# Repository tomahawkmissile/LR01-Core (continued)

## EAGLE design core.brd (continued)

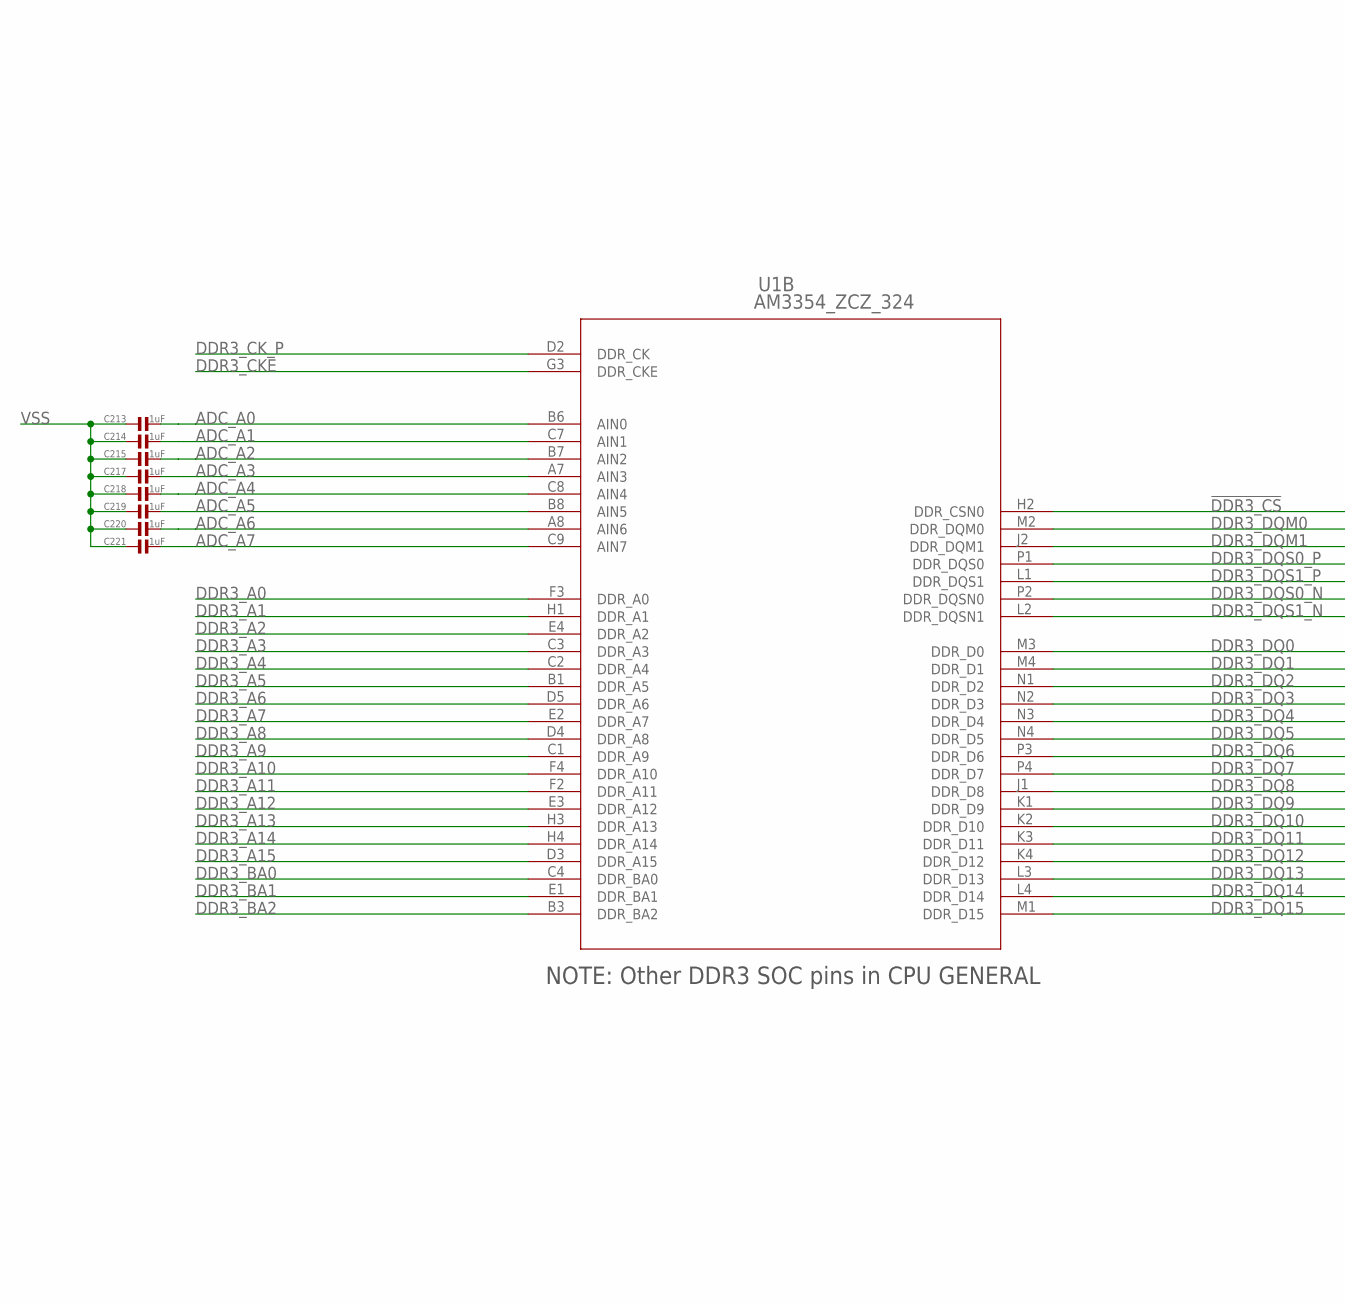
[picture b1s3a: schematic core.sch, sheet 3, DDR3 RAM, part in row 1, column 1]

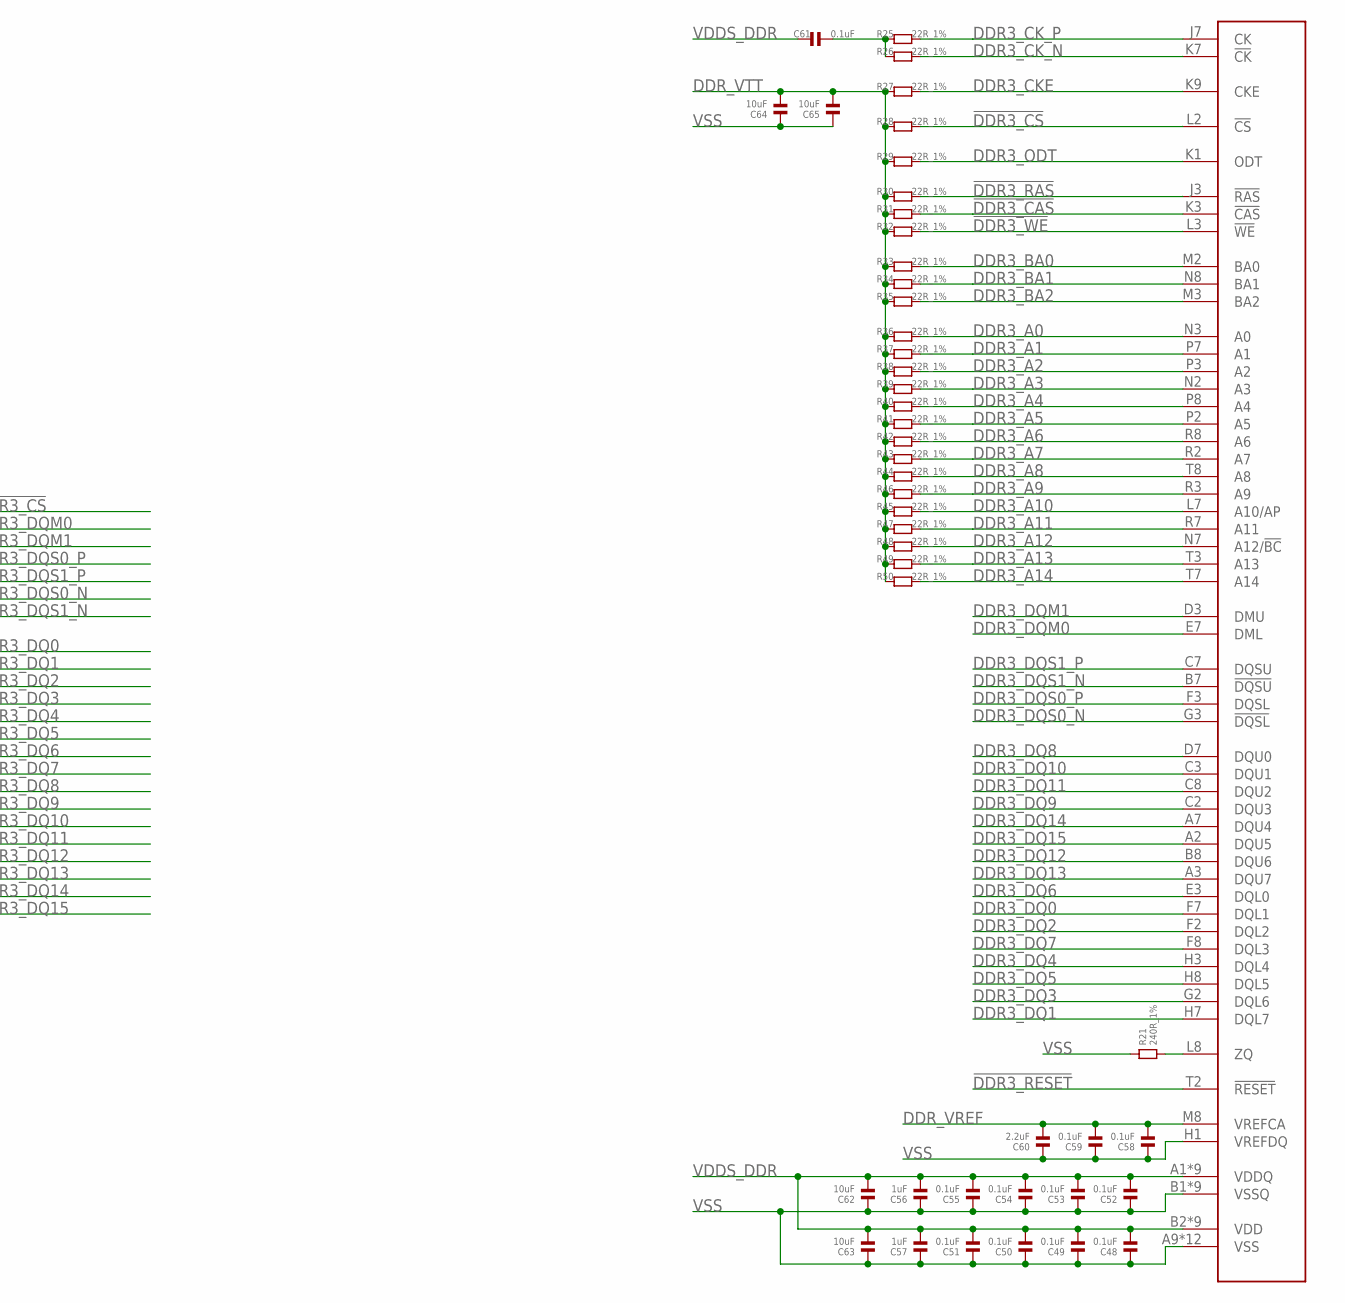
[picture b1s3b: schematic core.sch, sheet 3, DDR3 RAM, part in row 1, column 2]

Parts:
C48, C49, C50, C51, C52, C53, C54, C55, C59: 0.1uF; 0402
C56, C57, C213, C214, C215, C217, C218, C219, C220, C221: 1uF; 0402
C58, C61: 0.1uF; 0201
C60: 2.2uF; 0603
C62, C63: 10uF; 0603
C64, C65: 10uF; 0402
R21: 240R_1%; 0402
R25, R26, R27, R28, R29, R30, R31, R32, R33, R34, R35, R36, R37, R38, R39, R40, R41, R42, R43, R44, R45, R46, R47, R48, R49, R50: 22R_1%; 0201
U1: AM3354_ZCZ_324; ZCZ324
U9: AS4C256M16D3B-12BIN; BGA144C80P9X16_1350X900X120

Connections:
!DDR3_CAS: R31.2, U9.K3 (!CAS); also elsewhere on the board
!DDR3_CS: R28.2, U1.H2 (DDR_CSN0), U9.L2 (!CS)
!DDR3_RAS: R30.2, U9.J3 (!RAS); also elsewhere on the board
!DDR3_RESET: U9.T2 (!RESET); also elsewhere on the board
!DDR3_WE: R32.2, U9.L3 (!WE); also elsewhere on the board
ADC_A0: C213.2, U1.B6 (AIN0); also elsewhere on the board
ADC_A1: C214.2, U1.C7 (AIN1); also elsewhere on the board
ADC_A2: C215.2, U1.B7 (AIN2); also elsewhere on the board
ADC_A3: C217.2, U1.A7 (AIN3); also elsewhere on the board
ADC_A4: C218.2, U1.C8 (AIN4); also elsewhere on the board
ADC_A5: C219.2, U1.B8 (AIN5); also elsewhere on the board
ADC_A6: C220.2, U1.A8 (AIN6); also elsewhere on the board
ADC_A7: C221.2, U1.C9 (AIN7); also elsewhere on the board
DDR3_A0: R36.2, U1.F3 (DDR_A0), U9.N3 (A0)
DDR3_A1: R37.2, U1.H1 (DDR_A1), U9.P7 (A1)
DDR3_A2: R38.2, U1.E4 (DDR_A2), U9.P3 (A2)
DDR3_A3: R39.2, U1.C3 (DDR_A3), U9.N2 (A3)
DDR3_A4: R40.2, U1.C2 (DDR_A4), U9.P8 (A4)
DDR3_A5: R41.2, U1.B1 (DDR_A5), U9.P2 (A5)
DDR3_A6: R42.2, U1.D5 (DDR_A6), U9.R8 (A6)
DDR3_A7: R43.2, U1.E2 (DDR_A7), U9.R2 (A7)
DDR3_A8: R44.2, U1.D4 (DDR_A8), U9.T8 (A8)
DDR3_A9: R46.2, U1.C1 (DDR_A9), U9.R3 (A9)
DDR3_A10: R45.2, U1.F4 (DDR_A10), U9.L7 (A10/AP)
DDR3_A11: R47.2, U1.F2 (DDR_A11), U9.R7 (A11)
DDR3_A12: R48.2, U1.E3 (DDR_A12), U9.N7 (A12/!BC)
DDR3_A13: R49.2, U1.H3 (DDR_A13), U9.T3 (A13)
DDR3_A14: R50.2, U1.H4 (DDR_A14), U9.T7 (A14)
DDR3_A15: U1.D3 (DDR_A15)
DDR3_BA0: R33.2, U1.C4 (DDR_BA0), U9.M2 (BA0)
DDR3_BA1: R34.2, U1.E1 (DDR_BA1), U9.N8 (BA1)
DDR3_BA2: R35.2, U1.B3 (DDR_BA2), U9.M3 (BA2)
DDR3_CKE: R27.2, U1.G3 (DDR_CKE), U9.K9 (CKE)
DDR3_CK_N: R26.2, U9.K7 (!CK); also elsewhere on the board
DDR3_CK_P: R25.2, U1.D2 (DDR_CK), U9.J7 (CK)
DDR3_DQ0: U1.M3 (DDR_D0), U9.F7 (DQL1)
DDR3_DQ1: U1.M4 (DDR_D1), U9.H7 (DQL7)
DDR3_DQ2: U1.N1 (DDR_D2), U9.F2 (DQL2)
DDR3_DQ3: U1.N2 (DDR_D3), U9.G2 (DQL6)
DDR3_DQ4: U1.N3 (DDR_D4), U9.H3 (DQL4)
DDR3_DQ5: U1.N4 (DDR_D5), U9.H8 (DQL5)
DDR3_DQ6: U1.P3 (DDR_D6), U9.E3 (DQL0)
DDR3_DQ7: U1.P4 (DDR_D7), U9.F8 (DQL3)
DDR3_DQ8: U1.J1 (DDR_D8), U9.D7 (DQU0)
DDR3_DQ9: U1.K1 (DDR_D9), U9.C2 (DQU3)
DDR3_DQ10: U1.K2 (DDR_D10), U9.C3 (DQU1)
DDR3_DQ11: U1.K3 (DDR_D11), U9.C8 (DQU2)
DDR3_DQ12: U1.K4 (DDR_D12), U9.B8 (DQU6)
DDR3_DQ13: U1.L3 (DDR_D13), U9.A3 (DQU7)
DDR3_DQ14: U1.L4 (DDR_D14), U9.A7 (DQU4)
DDR3_DQ15: U1.M1 (DDR_D15), U9.A2 (DQU5)
DDR3_DQM0: U1.M2 (DDR_DQM0), U9.E7 (DML)
DDR3_DQM1: U1.J2 (DDR_DQM1), U9.D3 (DMU)
DDR3_DQS0_N: U1.P2 (DDR_DQSN0), U9.G3 (!DQSL)
DDR3_DQS0_P: U1.P1 (DDR_DQS0), U9.F3 (DQSL)
DDR3_DQS1_N: U1.L2 (DDR_DQSN1), U9.B7 (!DQSU)
DDR3_DQS1_P: U1.L1 (DDR_DQS1), U9.C7 (DQSU)
DDR3_ODT: R29.2, U9.K1 (ODT); also elsewhere on the board
DDR_VREF: C58.2, C59.2, C60.2, U9.M8 (VREFCA); also elsewhere on the board
DDR_VTT: C64.2, C65.2, R27.1, R28.1, R29.1, R30.1, R31.1, R32.1, R33.1, R34.1, R35.1, R36.1, R37.1, R38.1, R39.1, R40.1, R41.1, R42.1, R43.1, R44.1, R45.1, R46.1, R47.1, R48.1, R49.1, R50.1; also elsewhere on the board
unnamed: R21.2, U9.L8 (ZQ)
unnamed: C61.2, R25.1, R26.1
VDDS_DDR: C48.2, C49.2, C50.2, C51.2, C52.2, C53.2, C54.2, C55.2, C56.2, C57.2, C61.1, C62.2, C63.2, U9.A1 (VDDQ), U9.A8 (VDDQ), U9.B2 (VDD), U9.C1 (VDDQ), U9.C9 (VDDQ), U9.D2 (VDDQ), U9.D9 (VDD), U9.E9 (VDDQ), U9.F1 (VDDQ), U9.G7 (VDD), U9.H2 (VDDQ), U9.H9 (VDDQ), U9.K2 (VDD), U9.K8 (VDD), U9.N1 (VDD), U9.N9 (VDD), U9.R1 (VDD), U9.R9 (VDD); also elsewhere on the board
VPP: U1.M5 (VPP)
VSS: C48.1, C49.1, C50.1, C51.1, C52.1, C53.1, C54.1, C55.1, C56.1, C57.1, C58.1, C59.1, C60.1, C62.1, C63.1, C64.1, C65.1, C213.1, C214.1, C215.1, C217.1, C218.1, C219.1, C220.1, C221.1, R21.1, U9.A9 (VSS), U9.B1 (VSSQ), U9.B3 (VSS), U9.B9 (VSSQ), U9.D1 (VSSQ), U9.D8 (VSSQ), U9.E1 (VSS), U9.E2 (VSSQ), U9.E8 (VSSQ), U9.F9 (VSSQ), U9.G1 (VSSQ), U9.G8 (VSS), U9.G9 (VSSQ), U9.H1 (VREFDQ), U9.J2 (VSS), U9.J8 (VSS), U9.M1 (VSS), U9.M9 (VSS), U9.P1 (VSS), U9.P9 (VSS), U9.T1 (VSS), U9.T9 (VSS); also elsewhere on the board

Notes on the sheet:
NOTE: Other DDR3 SOC pins in CPU GENERAL

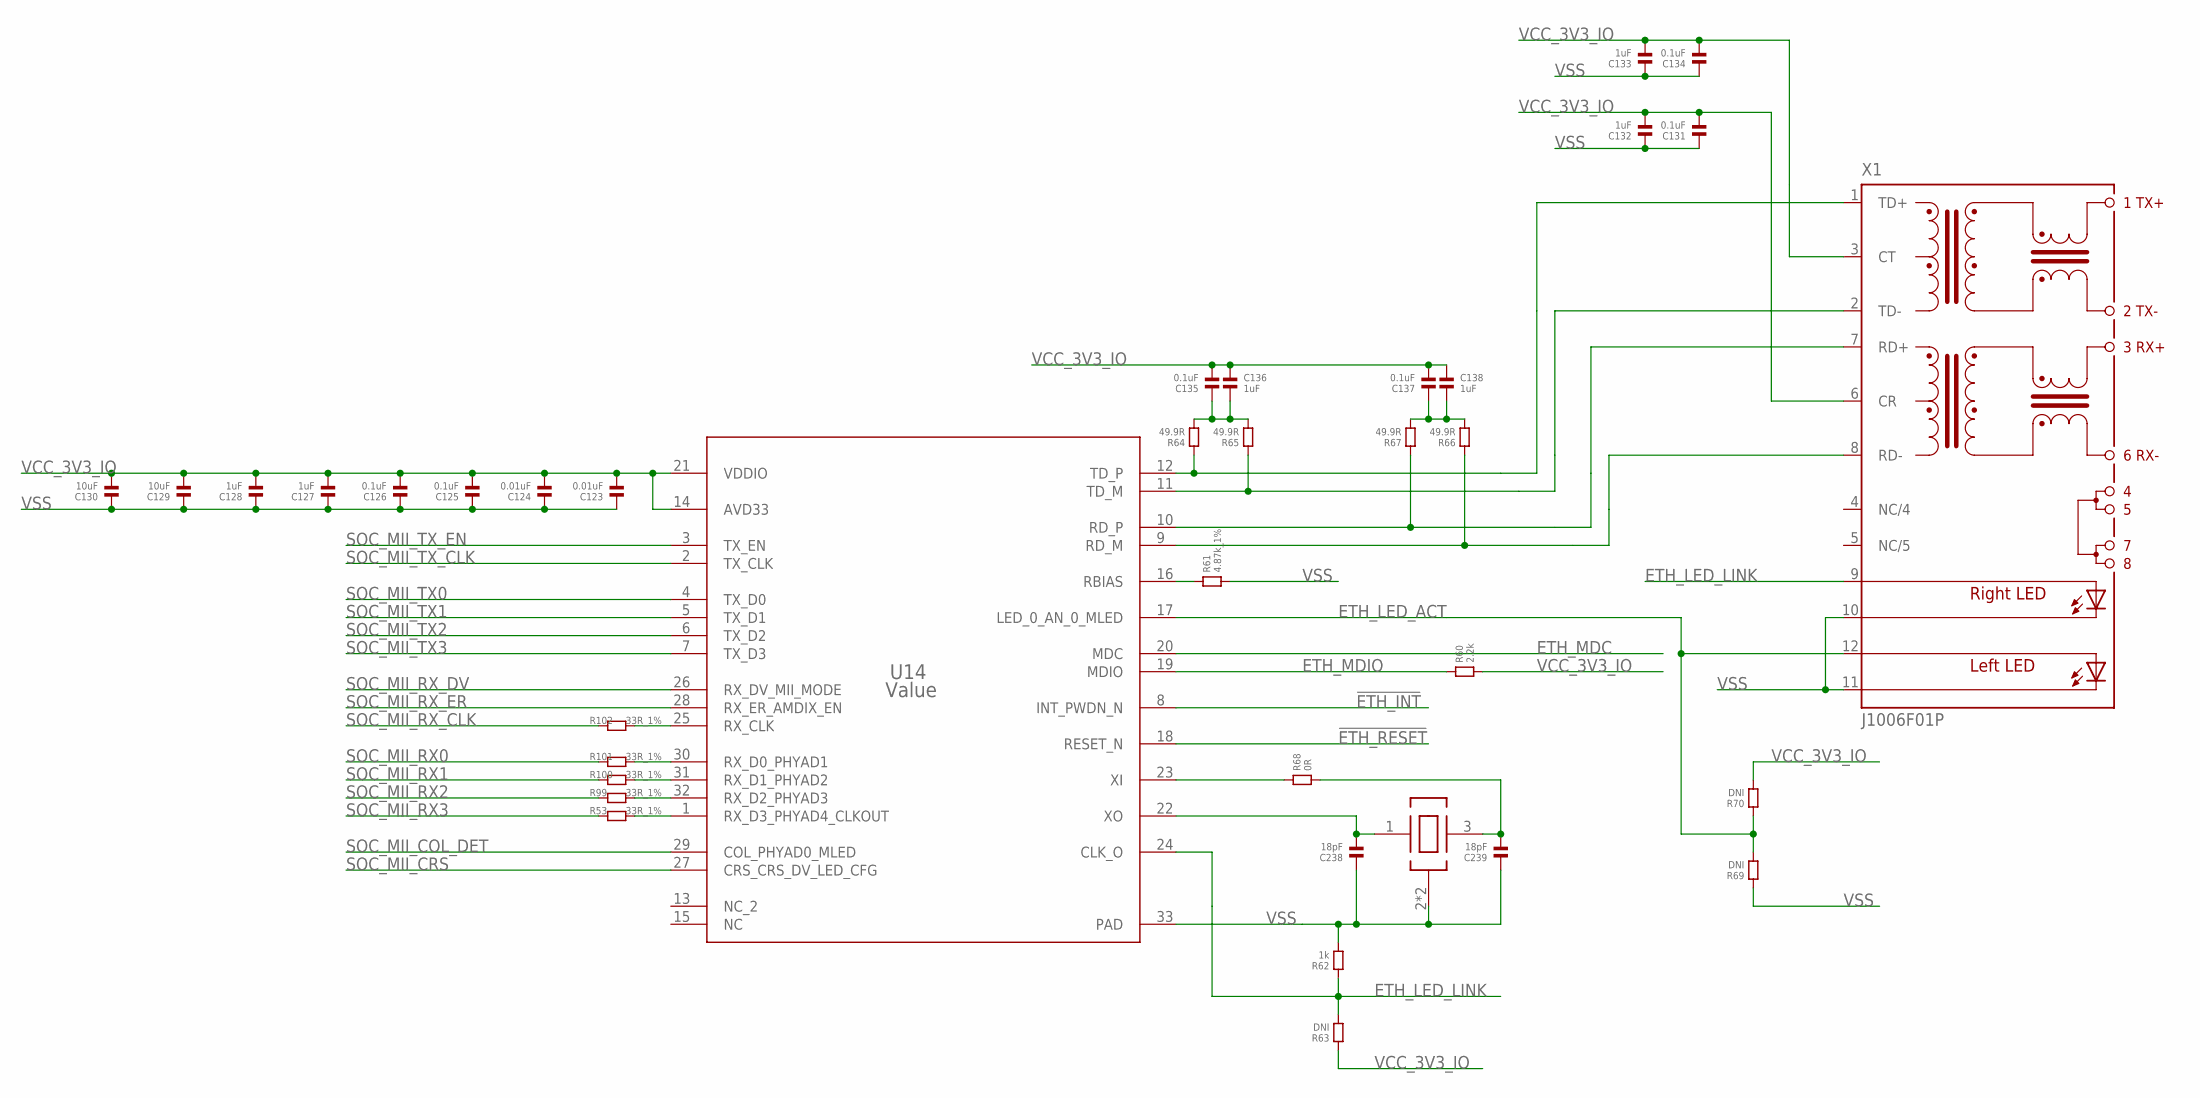
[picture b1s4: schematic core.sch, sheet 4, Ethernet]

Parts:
C123, C124: 0.01uF; 0402
C125, C126, C131, C134, C135, C137: 0.1uF; 0402
C127, C128, C132, C133, C136, C138: 1uF; 0402
C129, C130: 10uF; 0402
C238, C239: 18pF; 0402
R53, R99, R100, R101, R102: 33R_1%; 0402
R60: 2.2k; 0402
R61: 4.87k_1%; 0402
R62: 1k; 0402
R63, R69, R70: DNI; 0402
R64, R65, R66, R67: 49.9R; 0402
R68: 0R; 0402
U14: Value; RHB0032B
U$7: ECS-250-18-36B-CKY-TR; OSCCC250X200X65
X1: J1006F01P; J1

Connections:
!ETH_INT: U14.8 (INT_PWDN_N); also elsewhere on the board
!ETH_RESET: U14.18 (RESET_N); also elsewhere on the board
ETH_LED_ACT: R69.2, R70.1, U14.17 (LED_0_AN_0_MLED), X1.12 (A-L)
ETH_LED_LINK: R62.1, R63.2, U14.24 (CLK_O), X1.9 (A-R)
ETH_MDC: U14.20 (MDC); also elsewhere on the board
ETH_MDIO: R60.1, U14.19 (MDIO); also elsewhere on the board
unnamed: R61.1, U14.16 (RBIAS)
unnamed: C238.2, U14.22 (XO), U$7.1 (XI)
unnamed: C239.2, R68.2, U$7.3 (XO)
unnamed: R66.1, U14.9 (RD_M), X1.8 (RD-)
unnamed: R67.1, U14.10 (RD_P), X1.7 (RD+)
unnamed: C135.1, C136.2, R64.2, R65.2
unnamed: R68.1, U14.23 (XI)
unnamed: C137.1, C138.2, R66.2, R67.2
unnamed: R65.1, U14.11 (TD_M), X1.2 (TD-)
unnamed: R64.1, U14.12 (TD_P), X1.1 (TD+)
unnamed: R53.2, U14.1 (RX_D3_PHYAD4_CLKOUT)
unnamed: R99.2, U14.32 (RX_D2_PHYAD3)
unnamed: R100.2, U14.31 (RX_D1_PHYAD2)
unnamed: R101.2, U14.30 (RX_D0_PHYAD1)
unnamed: R102.2, U14.25 (RX_CLK)
SOC_MII_COL_DET: U14.29 (COL_PHYAD0_MLED); also elsewhere on the board
SOC_MII_CRS: U14.27 (CRS_CRS_DV_LED_CFG); also elsewhere on the board
SOC_MII_RX0: R101.1; also elsewhere on the board
SOC_MII_RX1: R100.1; also elsewhere on the board
SOC_MII_RX2: R99.1; also elsewhere on the board
SOC_MII_RX3: R53.1; also elsewhere on the board
SOC_MII_RX_CLK: R102.1; also elsewhere on the board
SOC_MII_RX_DV: U14.26 (RX_DV_MII_MODE); also elsewhere on the board
SOC_MII_RX_ER: U14.28 (RX_ER_AMDIX_EN); also elsewhere on the board
SOC_MII_TX0: U14.4 (TX_D0); also elsewhere on the board
SOC_MII_TX1: U14.5 (TX_D1); also elsewhere on the board
SOC_MII_TX2: U14.6 (TX_D2); also elsewhere on the board
SOC_MII_TX3: U14.7 (TX_D3); also elsewhere on the board
SOC_MII_TX_CLK: U14.2 (TX_CLK); also elsewhere on the board
SOC_MII_TX_EN: U14.3 (TX_EN); also elsewhere on the board
VCC_3V3_IO: C123.2, C124.2, C125.2, C126.2, C127.2, C128.2, C129.2, C130.2, C131.2, C132.2, C133.2, C134.2, C135.2, C136.1, C137.2, C138.1, R60.2, R63.1, R70.2, U14.14 (AVD33), U14.21 (VDDIO), X1.3 (CT), X1.6 (CR); also elsewhere on the board
VSS: C123.1, C124.1, C125.1, C126.1, C127.1, C128.1, C129.1, C130.1, C131.1, C132.1, C133.1, C134.1, C238.1, C239.1, R61.2, R62.2, R69.1, U14.33 (PAD), U$7.2 (VSS), U$7.4 (VSS), X1.10 (C-R), X1.11 (C-L); also elsewhere on the board

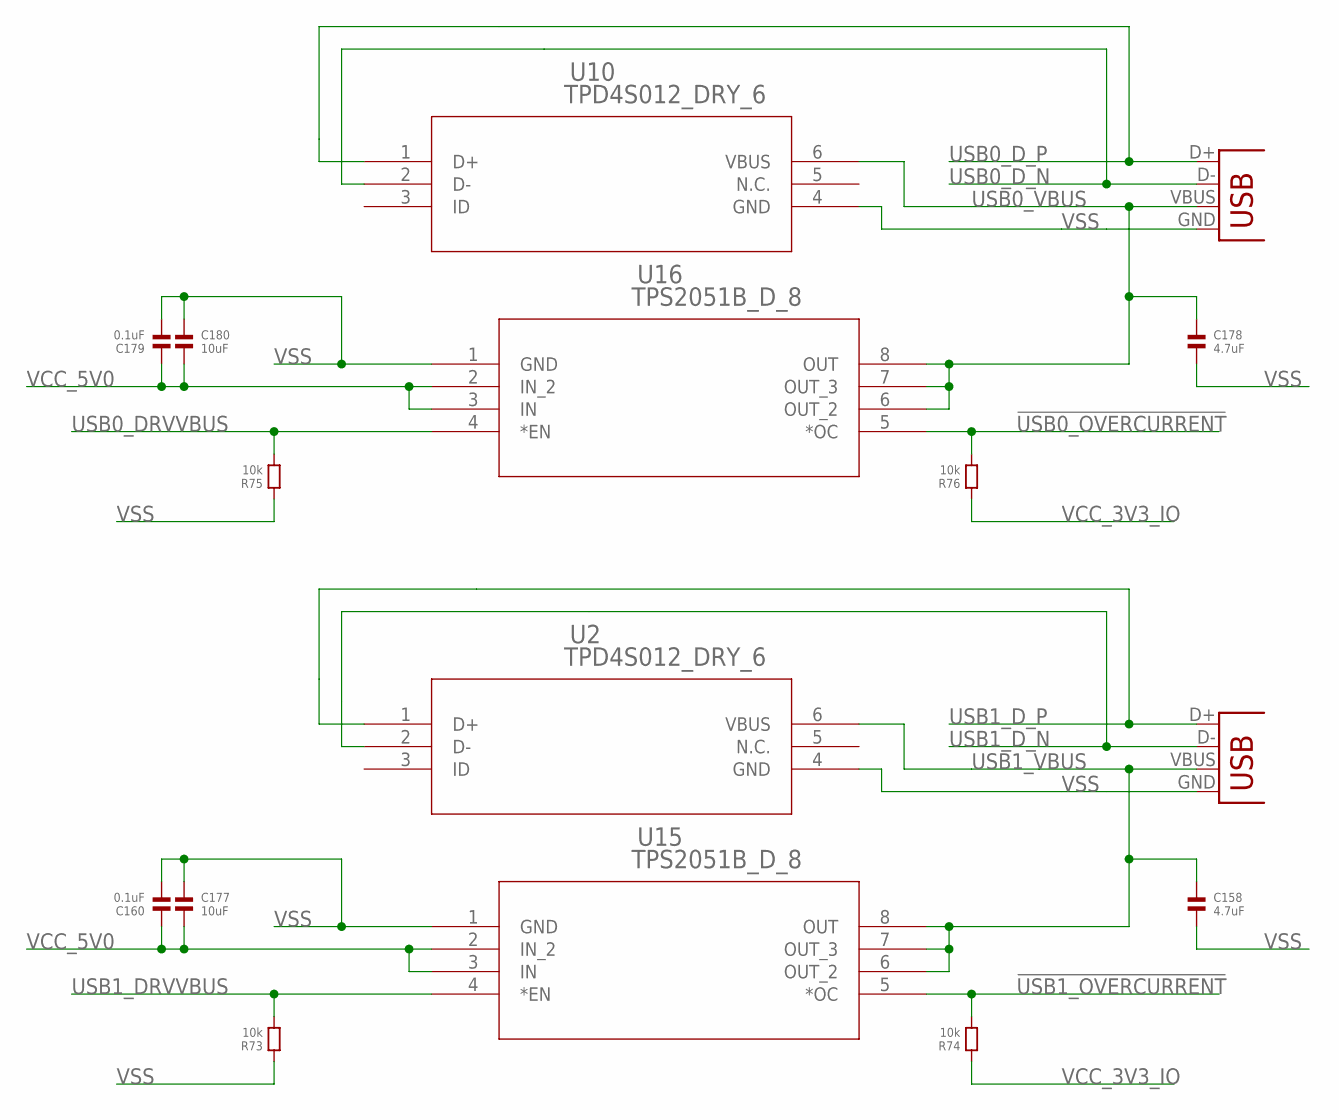
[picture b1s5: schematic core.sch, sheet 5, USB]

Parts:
C158, C178: 4.7uF; 0603
C160, C179: 0.1uF; 0603
C177, C180: 10uF; 0603
R73, R74, R75, R76: 10k; 0402
U2, U10: TPD4S012_DRY_6; DRY6
U15, U16: TPS2051B_D_8; D8
X2, X3: USB-A-H

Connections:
!USB0_OVERCURRENT: R76.2, U16.5 (*OC); also elsewhere on the board
!USB1_OVERCURRENT: R74.2, U15.5 (*OC); also elsewhere on the board
USB0_DRVVBUS: R75.2, U16.4 (*EN); also elsewhere on the board
USB0_D_N: U10.2 (D-), X3.D-; also elsewhere on the board
USB0_D_P: U10.1 (D+), X3.D+; also elsewhere on the board
USB0_VBUS: C178.1, U10.6 (VBUS), U16.6 (OUT_2), U16.7 (OUT_3), U16.8 (OUT), X3.VBUS; also elsewhere on the board
USB1_DRVVBUS: R73.2, U15.4 (*EN); also elsewhere on the board
USB1_D_N: U2.2 (D-), X2.D-; also elsewhere on the board
USB1_D_P: U2.1 (D+), X2.D+; also elsewhere on the board
USB1_VBUS: C158.1, U2.6 (VBUS), U15.6 (OUT_2), U15.7 (OUT_3), U15.8 (OUT), X2.VBUS; also elsewhere on the board
VCC_3V3_IO: R74.1, R76.1; also elsewhere on the board
VCC_5V0: C160.1, C177.2, C179.1, C180.2, U15.2 (IN_2), U15.3 (IN), U16.2 (IN_2), U16.3 (IN); also elsewhere on the board
VSS: C158.2, C160.2, C177.1, C178.2, C179.2, C180.1, R73.1, R75.1, U2.4 (GND), U10.4 (GND), U15.1 (GND), U16.1 (GND), X2.GND, X3.GND; also elsewhere on the board

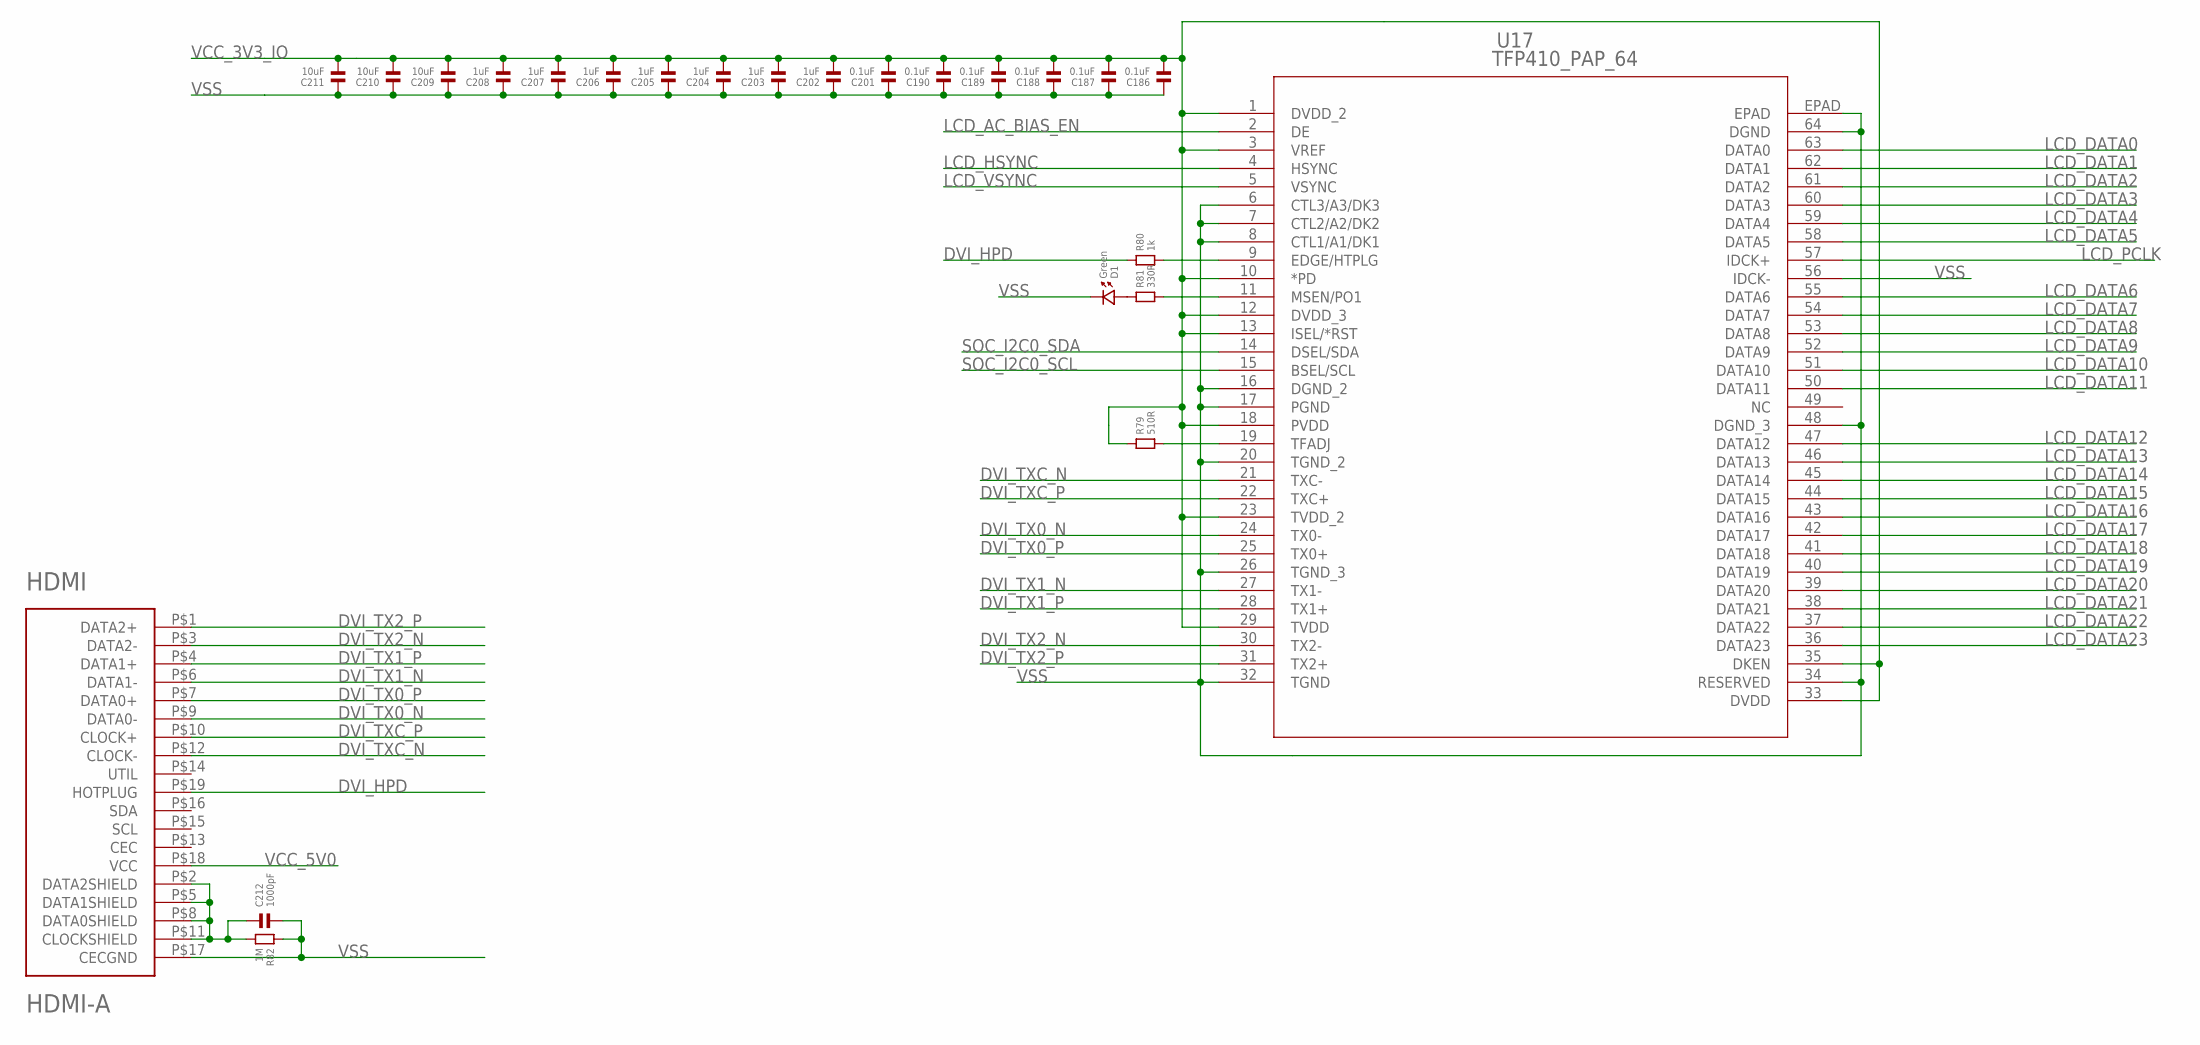
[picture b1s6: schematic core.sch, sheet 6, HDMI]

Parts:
C186, C187, C188, C189, C190, C201: 0.1uF; 0402
C202, C203, C204, C205, C206, C207, C208: 1uF; 0402
C209, C210, C211: 10uF; 0603
C212: 1000pF; 0402
D1: Green; 0603.LED
HDMI: HDMI-A; HDMI_A
R79: 510R; 0402
R80: 1k; 0402
R81: 330R; 0402
R82: 1M; 0402
U17: TFP410_PAP_64; PAP64_5X5

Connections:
DVI_HPD: HDMI.P$19 (HOTPLUG), R80.1
DVI_TX0_N: HDMI.P$9 (DATA0-), U17.24 (TX0-)
DVI_TX0_P: HDMI.P$7 (DATA0+), U17.25 (TX0+)
DVI_TX1_N: HDMI.P$6 (DATA1-), U17.27 (TX1-)
DVI_TX1_P: HDMI.P$4 (DATA1+), U17.28 (TX1+)
DVI_TX2_N: HDMI.P$3 (DATA2-), U17.30 (TX2-)
DVI_TX2_P: HDMI.P$1 (DATA2+), U17.31 (TX2+)
DVI_TXC_N: HDMI.P$12 (CLOCK-), U17.21 (TXC-)
DVI_TXC_P: HDMI.P$10 (CLOCK+), U17.22 (TXC+)
LCD_AC_BIAS_EN: U17.2 (DE); also elsewhere on the board
LCD_DATA0: U17.63 (DATA0); also elsewhere on the board
LCD_DATA1: U17.62 (DATA1); also elsewhere on the board
LCD_DATA2: U17.61 (DATA2); also elsewhere on the board
LCD_DATA3: U17.60 (DATA3); also elsewhere on the board
LCD_DATA4: U17.59 (DATA4); also elsewhere on the board
LCD_DATA5: U17.58 (DATA5); also elsewhere on the board
LCD_DATA6: U17.55 (DATA6); also elsewhere on the board
LCD_DATA7: U17.54 (DATA7); also elsewhere on the board
LCD_DATA8: U17.53 (DATA8); also elsewhere on the board
LCD_DATA9: U17.52 (DATA9); also elsewhere on the board
LCD_DATA10: U17.51 (DATA10); also elsewhere on the board
LCD_DATA11: U17.50 (DATA11); also elsewhere on the board
LCD_DATA12: U17.47 (DATA12); also elsewhere on the board
LCD_DATA13: U17.46 (DATA13); also elsewhere on the board
LCD_DATA14: U17.45 (DATA14); also elsewhere on the board
LCD_DATA15: U17.44 (DATA15); also elsewhere on the board
LCD_DATA16: U17.43 (DATA16); also elsewhere on the board
LCD_DATA17: U17.42 (DATA17); also elsewhere on the board
LCD_DATA18: U17.41 (DATA18); also elsewhere on the board
LCD_DATA19: U17.40 (DATA19); also elsewhere on the board
LCD_DATA20: U17.39 (DATA20); also elsewhere on the board
LCD_DATA21: U17.38 (DATA21); also elsewhere on the board
LCD_DATA22: U17.37 (DATA22); also elsewhere on the board
LCD_DATA23: U17.36 (DATA23); also elsewhere on the board
LCD_HSYNC: U17.4 (HSYNC); also elsewhere on the board
LCD_PCLK: U17.57 (IDCK+); also elsewhere on the board
LCD_VSYNC: U17.5 (VSYNC); also elsewhere on the board
unnamed: R79.2, U17.19 (TFADJ)
unnamed: R80.2, U17.9 (EDGE/HTPLG)
unnamed: R81.2, U17.11 (MSEN/PO1)
unnamed: D1.P$1 (1), R81.1
unnamed: C212.1, HDMI.P$2 (DATA2SHIELD), HDMI.P$5 (DATA1SHIELD), HDMI.P$8 (DATA0SHIELD), HDMI.P$11 (CLOCKSHIELD), R82.2
SOC_I2C0_SCL: U17.15 (BSEL/SCL); also elsewhere on the board
SOC_I2C0_SDA: U17.14 (DSEL/SDA); also elsewhere on the board
VCC_3V3_IO: C186.2, C187.2, C188.2, C189.2, C190.2, C201.2, C202.2, C203.2, C204.2, C205.2, C206.2, C207.2, C208.2, C209.2, C210.2, C211.2, R79.1, U17.1 (DVDD_2), U17.3 (VREF), U17.10 (*PD), U17.12 (DVDD_3), U17.13 (ISEL/*RST), U17.18 (PVDD), U17.23 (TVDD_2), U17.29 (TVDD), U17.33 (DVDD), U17.35 (DKEN); also elsewhere on the board
VCC_5V0: HDMI.P$18 (VCC); also elsewhere on the board
VSS: C186.1, C187.1, C188.1, C189.1, C190.1, C201.1, C202.1, C203.1, C204.1, C205.1, C206.1, C207.1, C208.1, C209.1, C210.1, C211.1, C212.2, D1.P$2 (2), HDMI.P$17 (CECGND), R82.1, U17.6 (CTL3/A3/DK3), U17.7 (CTL2/A2/DK2), U17.8 (CTL1/A1/DK1), U17.16 (DGND_2), U17.17 (PGND), U17.20 (TGND_2), U17.26 (TGND_3), U17.32 (TGND), U17.34 (RESERVED), U17.48 (DGND_3), U17.56 (IDCK-), U17.64 (DGND), U17.EPAD; also elsewhere on the board

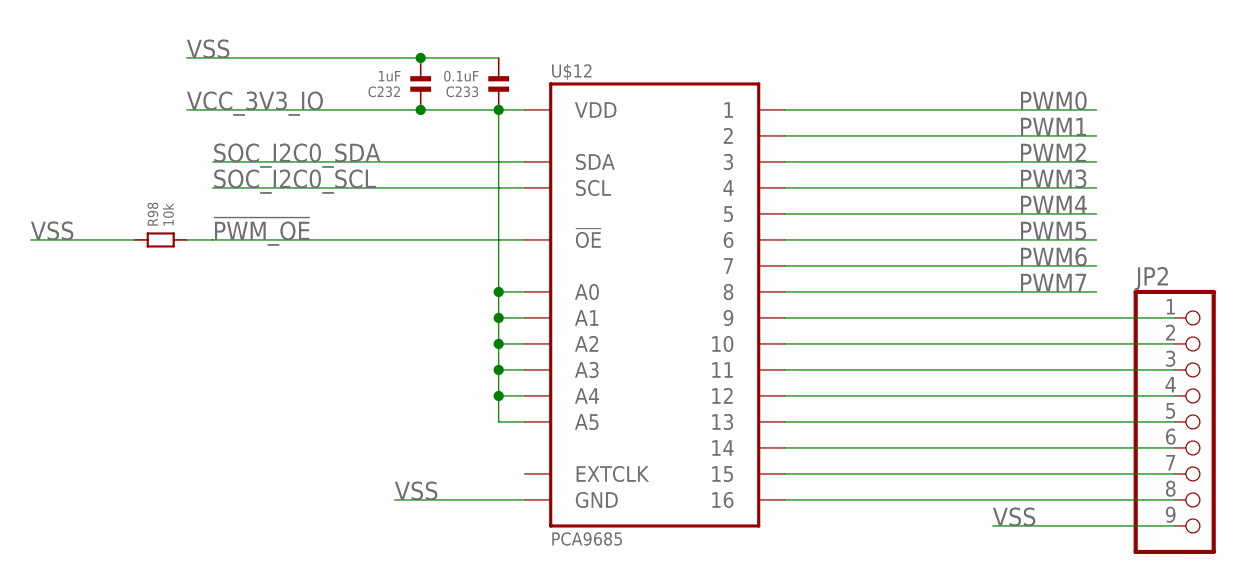
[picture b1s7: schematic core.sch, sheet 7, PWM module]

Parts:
C232: 1uF; 0402
C233: 0.1uF; 0402
JP2: PINHD-1X9; 1X09
R98: 10k; 0402
U$12: PCA9685; HVQFN28

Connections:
!PWM_OE: R98.2, U$12.23 (!OE)
unnamed: JP2.1, U$12.15 (9)
unnamed: JP2.2, U$12.16 (10)
unnamed: JP2.3, U$12.17 (11)
unnamed: JP2.5, U$12.19 (13)
unnamed: JP2.4, U$12.18 (12)
unnamed: JP2.6, U$12.20 (14)
unnamed: JP2.7, U$12.21 (15)
unnamed: JP2.8, U$12.22 (16)
PWM0: U$12.6 (1); also elsewhere on the board
PWM1: U$12.7 (2); also elsewhere on the board
PWM2: U$12.8 (3); also elsewhere on the board
PWM3: U$12.9 (4); also elsewhere on the board
PWM4: U$12.10 (5); also elsewhere on the board
PWM5: U$12.11 (6); also elsewhere on the board
PWM6: U$12.12 (7); also elsewhere on the board
PWM7: U$12.13 (8); also elsewhere on the board
SOC_I2C0_SCL: U$12.26 (SCL); also elsewhere on the board
SOC_I2C0_SDA: U$12.27 (SDA); also elsewhere on the board
VCC_3V3_IO: C232.1, C233.1, U$12.1 (A0), U$12.2 (A1), U$12.3 (A2), U$12.4 (A3), U$12.5 (A4), U$12.24 (A5), U$12.28 (VDD); also elsewhere on the board
VSS: C232.2, C233.2, JP2.9, R98.1, U$12.14 (GND), U$12.PAD (GND); also elsewhere on the board

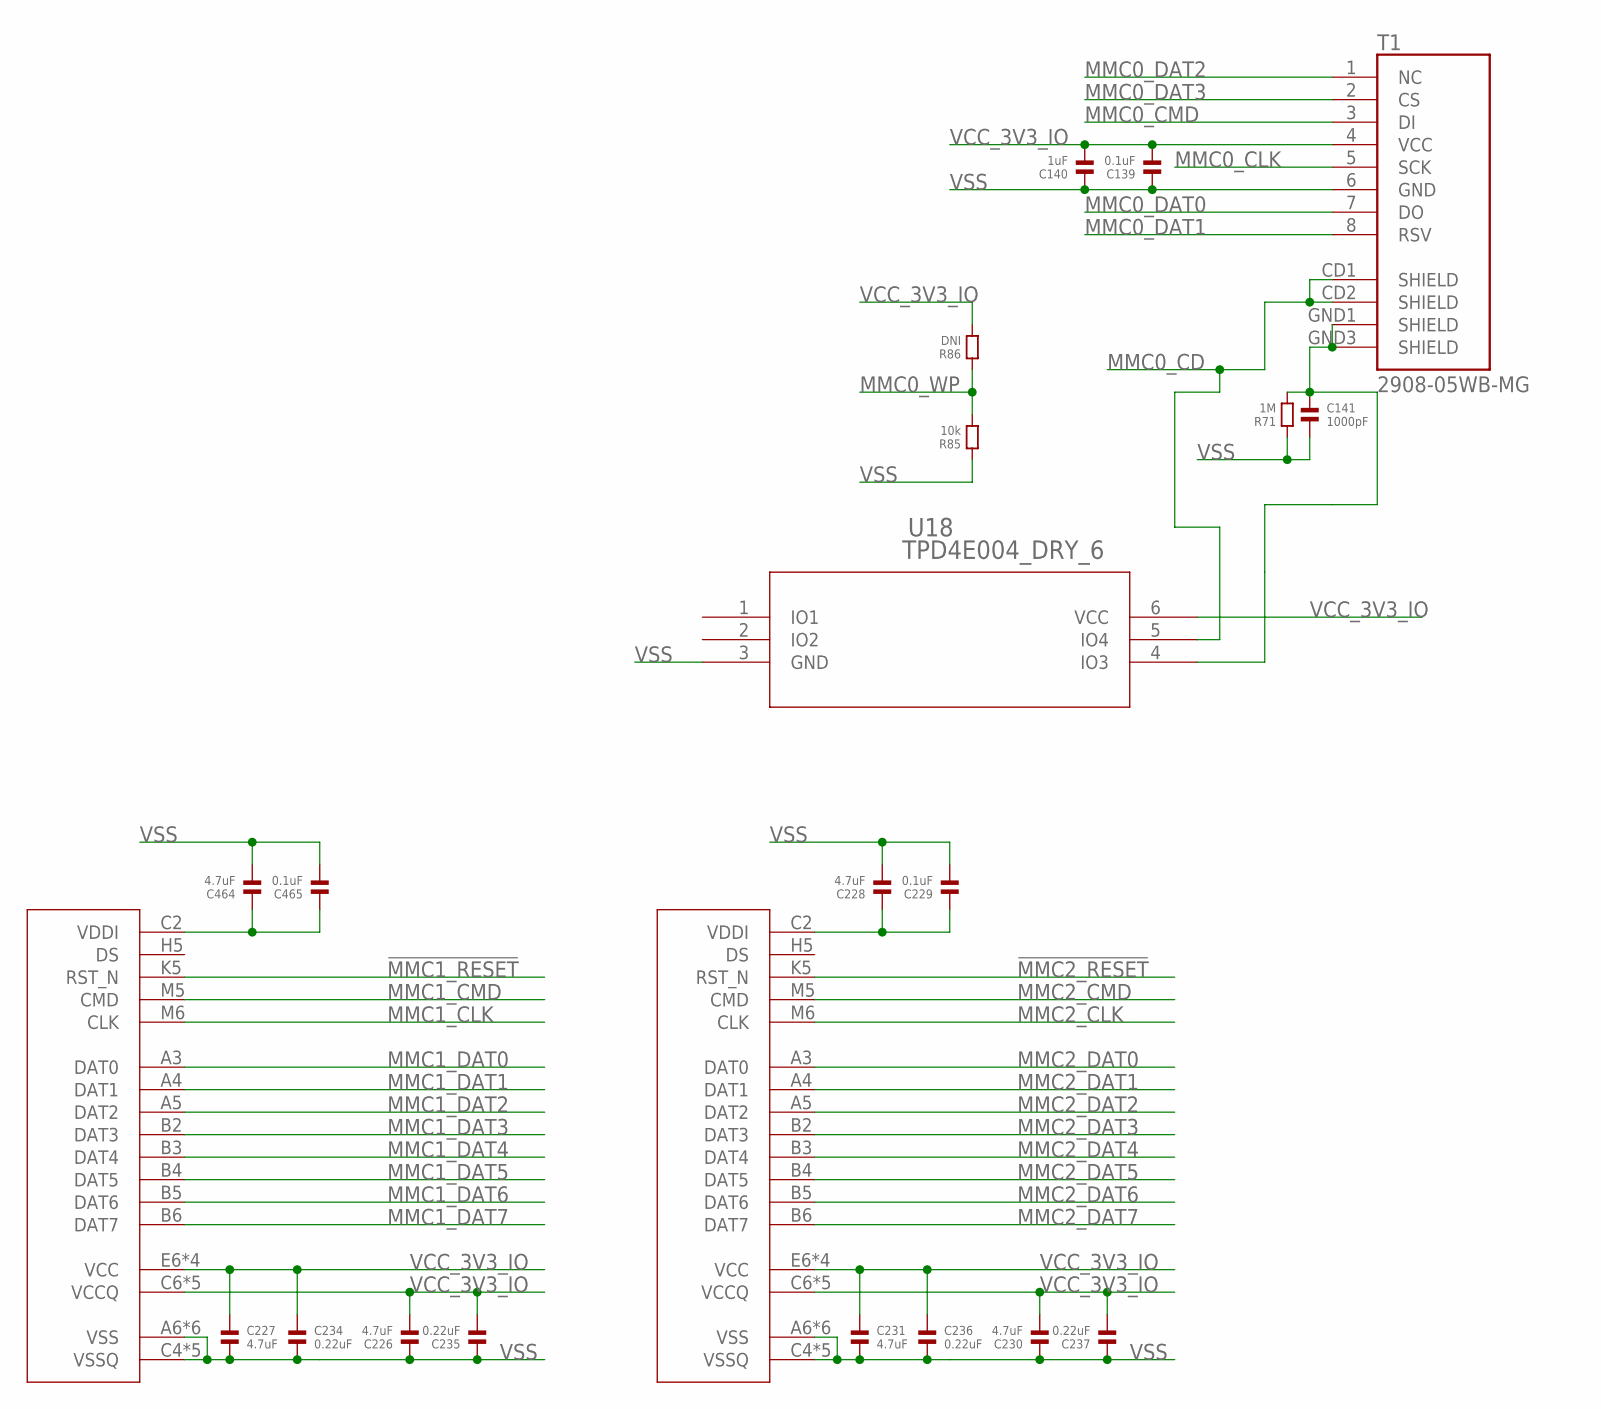
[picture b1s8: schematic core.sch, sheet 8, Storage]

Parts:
C139: 0.1uF; 0402
C140: 1uF; 0402
C141: 1000pF; 0402
C226, C227, C228, C230, C231, C464: 4.7uF; 0603
C229, C465: 0.1uF; 0603
C234, C235, C236, C237: 0.22uF; 0603
R71: 1M; 0402
R85: 10k; 0402
R86: DNI; 0402
T1: 2908-05WB-MG; MICRO-SD-SOCKET-PP
U18: TPD4E004_DRY_6; DRY6
U$10, U$11: IS21ES16G; BGA153C50P14X14_1150X1300X100N

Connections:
!MMC1_RESET: U$10.K5 (RST_N); also elsewhere on the board
!MMC2_RESET: U$11.K5 (RST_N); also elsewhere on the board
MMC0_CD: T1.CD1 (SHIELD), T1.CD2 (SHIELD), U18.5 (IO4); also elsewhere on the board
MMC0_CLK: T1.5 (SCK); also elsewhere on the board
MMC0_CMD: T1.3 (DI); also elsewhere on the board
MMC0_DAT0: T1.7 (DO); also elsewhere on the board
MMC0_DAT1: T1.8 (RSV); also elsewhere on the board
MMC0_DAT2: T1.1 (NC); also elsewhere on the board
MMC0_DAT3: T1.2 (CS); also elsewhere on the board
MMC0_WP: R85.2, R86.1; also elsewhere on the board
MMC1_CLK: U$10.M6 (CLK); also elsewhere on the board
MMC1_CMD: U$10.M5 (CMD); also elsewhere on the board
MMC1_DAT0: U$10.A3 (DAT0); also elsewhere on the board
MMC1_DAT1: U$10.A4 (DAT1); also elsewhere on the board
MMC1_DAT2: U$10.A5 (DAT2); also elsewhere on the board
MMC1_DAT3: U$10.B2 (DAT3); also elsewhere on the board
MMC1_DAT4: U$10.B3 (DAT4); also elsewhere on the board
MMC1_DAT5: U$10.B4 (DAT5); also elsewhere on the board
MMC1_DAT6: U$10.B5 (DAT6); also elsewhere on the board
MMC1_DAT7: U$10.B6 (DAT7); also elsewhere on the board
MMC2_CLK: U$11.M6 (CLK); also elsewhere on the board
MMC2_CMD: U$11.M5 (CMD); also elsewhere on the board
MMC2_DAT0: U$11.A3 (DAT0); also elsewhere on the board
MMC2_DAT1: U$11.A4 (DAT1); also elsewhere on the board
MMC2_DAT2: U$11.A5 (DAT2); also elsewhere on the board
MMC2_DAT3: U$11.B2 (DAT3); also elsewhere on the board
MMC2_DAT4: U$11.B3 (DAT4); also elsewhere on the board
MMC2_DAT5: U$11.B4 (DAT5); also elsewhere on the board
MMC2_DAT6: U$11.B5 (DAT6); also elsewhere on the board
MMC2_DAT7: U$11.B6 (DAT7); also elsewhere on the board
unnamed: C141.1, R71.2, T1.GND1 (SHIELD), T1.GND3 (SHIELD), U18.4 (IO3)
unnamed: C464.1, C465.1, U$10.C2 (VDDI)
unnamed: C228.1, C229.1, U$11.C2 (VDDI)
VCC_3V3_IO: C139.2, C140.2, C226.2, C227.1, C230.2, C231.1, C234.1, C235.2, C236.1, C237.2, R86.2, T1.4 (VCC), U18.6 (VCC), U$10.C6 (VCCQ), U$10.E6 (VCC), U$10.F5 (VCC), U$10.J10 (VCC), U$10.K9 (VCC), U$10.M4 (VCCQ), U$10.N4 (VCCQ), U$10.P3 (VCCQ), U$10.P5 (VCCQ), U$11.C6 (VCCQ), U$11.E6 (VCC), U$11.F5 (VCC), U$11.J10 (VCC), U$11.K9 (VCC), U$11.M4 (VCCQ), U$11.N4 (VCCQ), U$11.P3 (VCCQ), U$11.P5 (VCCQ); also elsewhere on the board
VSS: C139.1, C140.1, C141.2, C226.1, C227.2, C228.2, C229.2, C230.1, C231.2, C234.2, C235.1, C236.2, C237.1, C464.2, C465.2, R71.1, R85.1, T1.6 (GND), U18.3 (GND), U$10.A6 (VSS), U$10.C4 (VSSQ), U$10.E7 (VSS), U$10.G5 (VSS), U$10.H10 (VSS), U$10.J5 (VSS), U$10.K8 (VSS), U$10.N2 (VSSQ), U$10.N5 (VSSQ), U$10.P4 (VSSQ), U$10.P6 (VSSQ), U$11.A6 (VSS), U$11.C4 (VSSQ), U$11.E7 (VSS), U$11.G5 (VSS), U$11.H10 (VSS), U$11.J5 (VSS), U$11.K8 (VSS), U$11.N2 (VSSQ), U$11.N5 (VSSQ), U$11.P4 (VSSQ), U$11.P6 (VSSQ); also elsewhere on the board
